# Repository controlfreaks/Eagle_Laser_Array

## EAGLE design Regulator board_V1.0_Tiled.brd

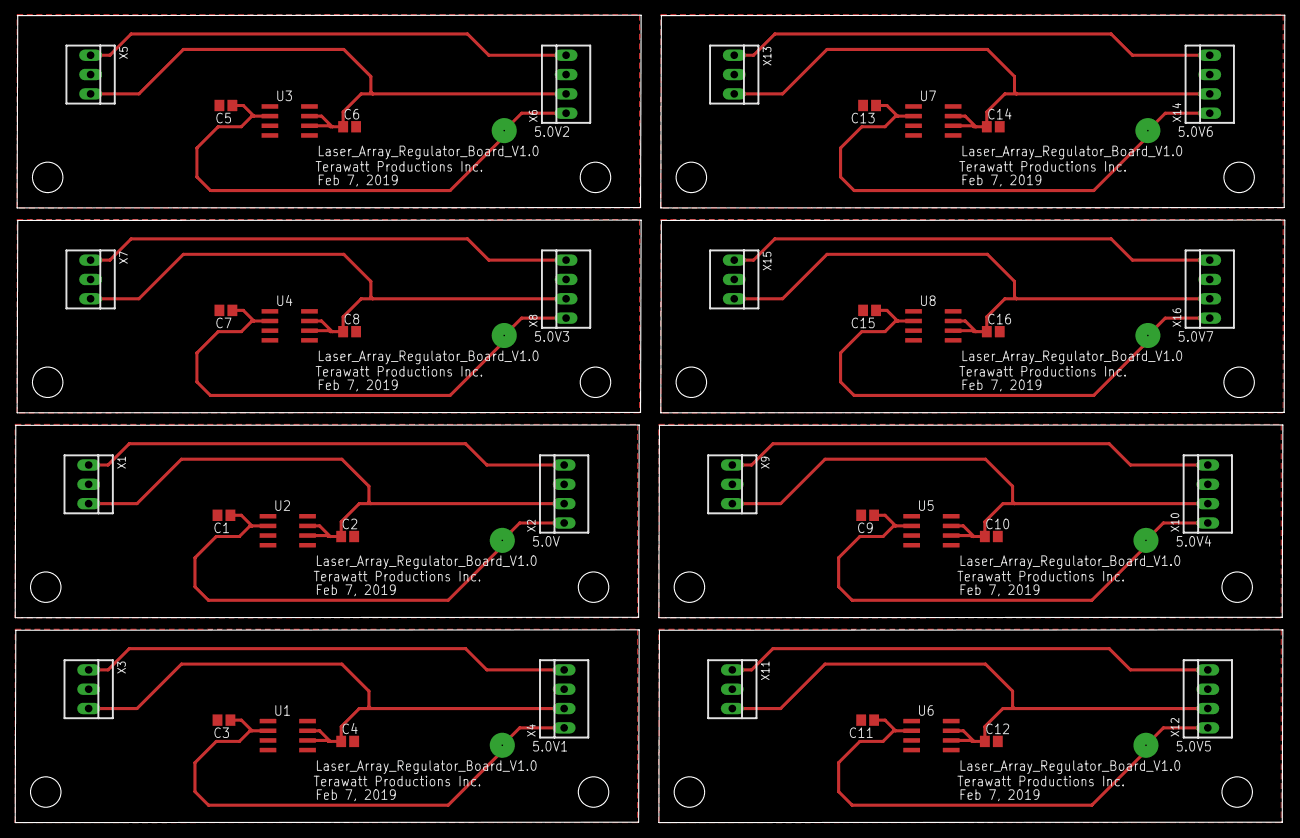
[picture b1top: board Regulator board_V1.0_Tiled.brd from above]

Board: 2 copper layers, 166.8 x 106.1 mm, 48 parts (0 on the bottom side), 32 nets.

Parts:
5.0V, 5.0V1, 5.0V2, 5.0V3, 5.0V4, 5.0V5, 5.0V6, 5.0V7: CONTACT-2MM
C1, C2, C3, C4, C5, C6, C7, C8, C9, C10, C11, C12, C13, C14, C15, C16: 1uF; C0805
U1, U2, U3, U4, U5, U6, U7, U8: VOLTAGE_REG_APD1154ADL; SOIC8
X1, X3, X5, X7, X9, X11, X13, X15: 22-23-2031
X2, X4, X6, X8, X10, X12, X14, X16: 22-23-2041

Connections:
GND: C1.2, C2.2, U2.1, U2.3, U2.4, U2.5, U2.8, X1.2, X2.3
GND1: C3.2, C4.2, U1.1, U1.3, U1.4, U1.5, U1.8, X3.2, X4.3
GND2: C5.2, C6.2, U3.1, U3.3, U3.4, U3.5, U3.8, X5.2, X6.3
GND3: C7.2, C8.2, U4.1, U4.3, U4.4, U4.5, U4.8, X7.2, X8.3
GND4: C9.2, C10.2, U5.1, U5.3, U5.4, U5.5, U5.8, X9.2, X10.3
GND5: C11.2, C12.2, U6.1, U6.3, U6.4, U6.5, U6.8, X11.2, X12.3
GND6: C13.2, C14.2, U7.1, U7.3, U7.4, U7.5, U7.8, X13.2, X14.3
GND7: C15.2, C16.2, U8.1, U8.3, U8.4, U8.5, U8.8, X15.2, X16.3
unnamed: X1.1, X2.4
unnamed: C2.1, U2.6, U2.7, X1.3, X2.2
unnamed: 5.0V.1, C1.1, U2.2, X2.1
unnamed: X3.1, X4.4
unnamed: C4.1, U1.6, U1.7, X3.3, X4.2
unnamed: 5.0V1.1, C3.1, U1.2, X4.1
unnamed: X5.1, X6.4
unnamed: C6.1, U3.6, U3.7, X5.3, X6.2
unnamed: 5.0V2.1, C5.1, U3.2, X6.1
unnamed: X7.1, X8.4
unnamed: C8.1, U4.6, U4.7, X7.3, X8.2
unnamed: 5.0V3.1, C7.1, U4.2, X8.1
unnamed: X9.1, X10.4
unnamed: C10.1, U5.6, U5.7, X9.3, X10.2
unnamed: 5.0V4.1, C9.1, U5.2, X10.1
unnamed: X11.1, X12.4
unnamed: C12.1, U6.6, U6.7, X11.3, X12.2
unnamed: 5.0V5.1, C11.1, U6.2, X12.1
unnamed: X13.1, X14.4
unnamed: C14.1, U7.6, U7.7, X13.3, X14.2
unnamed: 5.0V6.1, C13.1, U7.2, X14.1
unnamed: X15.1, X16.4
unnamed: C16.1, U8.6, U8.7, X15.3, X16.2
unnamed: 5.0V7.1, C15.1, U8.2, X16.1

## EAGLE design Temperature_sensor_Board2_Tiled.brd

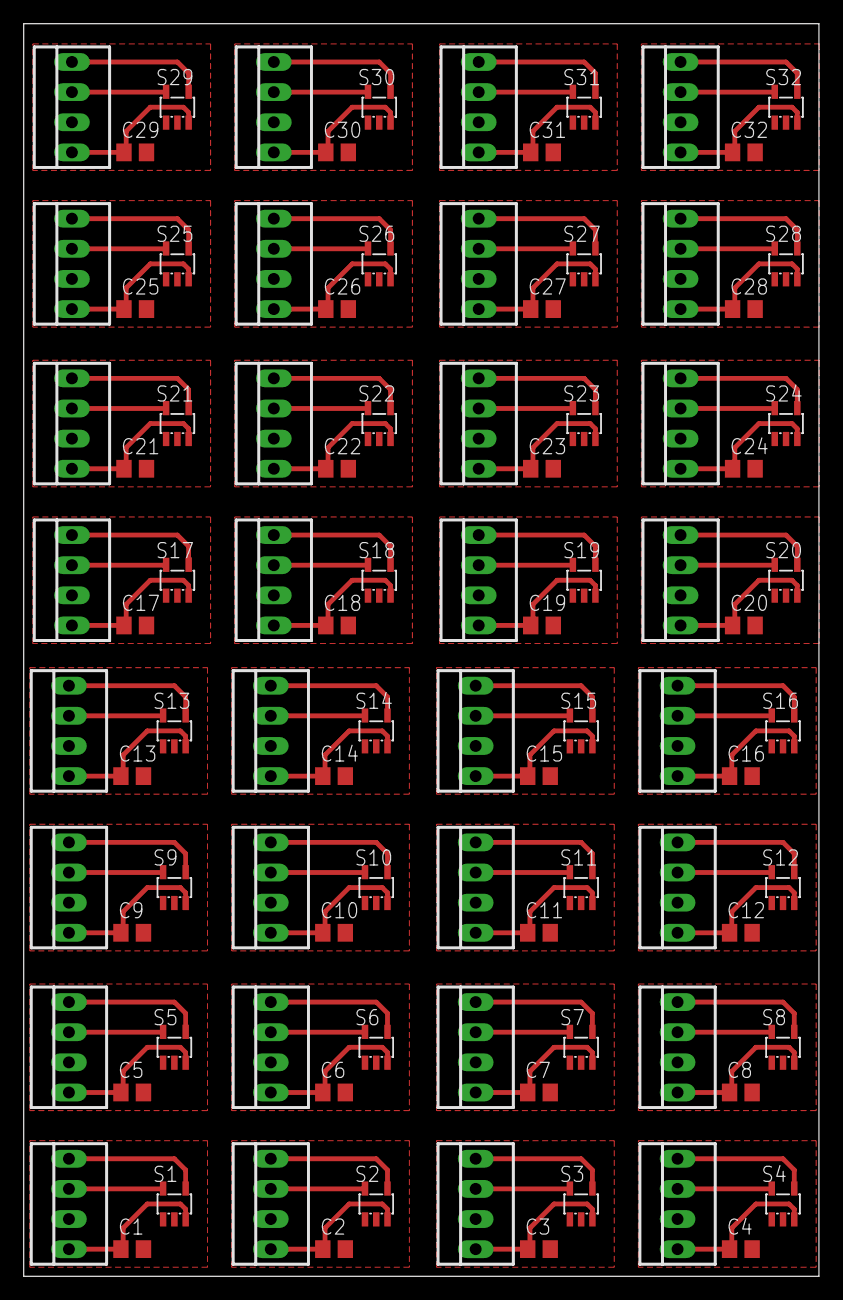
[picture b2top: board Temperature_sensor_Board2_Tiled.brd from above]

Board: 2 copper layers, 67.0 x 105.6 mm, 96 parts (0 on the bottom side), 128 nets.

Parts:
C1, C2, C3, C4, C5, C6, C7, C8, C9, C10, C11, C12, C13, C14, C15, C16, C17, C18, C19, C20, C21, C22, C23, C24, C25, C26, C27, C28, C29, C30, C31, C32: 0.01uF; C0805
S1, S2, S3, S4, S5, S6, S7, S8, S9, S10, S11, S12, S13, S14, S15, S16, S17, S18, S19, S20, S21, S22, S23, S24, S25, S26, S27, S28, S29, S30, S31, S32: TC74; SOT23-5L
X1, X2, X3, X4, X5, X6, X7, X8, X9, X10, X11, X12, X13, X14, X15, X16, X17, X18, X19, X20, X21, X22, X23, X24, X25, X26, X27, X28, X29, X30, X31, X32: 22-23-2041

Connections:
GND: C1.2, S1.2, X1.2
GND1: C2.2, S2.2, X2.2
GND2: C3.2, S3.2, X3.2
GND3: C4.2, S4.2, X4.2
GND4: C5.2, S5.2, X5.2
GND5: C6.2, S6.2, X6.2
GND6: C7.2, S7.2, X7.2
GND7: C8.2, S8.2, X8.2
GND8: C9.2, S9.2, X9.2
GND9: C10.2, S10.2, X10.2
GND10: C11.2, S11.2, X11.2
GND11: C12.2, S12.2, X12.2
GND12: C13.2, S13.2, X13.2
GND13: C14.2, S14.2, X14.2
GND14: C15.2, S15.2, X15.2
GND15: C16.2, S16.2, X16.2
GND16: C17.2, S17.2, X17.2
GND17: C18.2, S18.2, X18.2
GND18: C19.2, S19.2, X19.2
GND19: C20.2, S20.2, X20.2
GND20: C21.2, S21.2, X21.2
GND21: C22.2, S22.2, X22.2
GND22: C23.2, S23.2, X23.2
GND23: C24.2, S24.2, X24.2
GND24: C25.2, S25.2, X25.2
GND25: C26.2, S26.2, X26.2
GND26: C27.2, S27.2, X27.2
GND27: C28.2, S28.2, X28.2
GND28: C29.2, S29.2, X29.2
GND29: C30.2, S30.2, X30.2
GND30: C31.2, S31.2, X31.2
GND31: C32.2, S32.2, X32.2
unnamed: S2.5, X2.3
unnamed: C1.1, S1.3, X1.1
unnamed: S1.5, X1.3
unnamed: S1.4, X1.4
unnamed: S2.4, X2.4
unnamed: C2.1, S2.3, X2.1
unnamed: S3.5, X3.3
unnamed: S3.4, X3.4
unnamed: C3.1, S3.3, X3.1
unnamed: S4.5, X4.3
unnamed: S4.4, X4.4
unnamed: C4.1, S4.3, X4.1
unnamed: S5.5, X5.3
unnamed: S5.4, X5.4
unnamed: C5.1, S5.3, X5.1
unnamed: S6.5, X6.3
unnamed: S6.4, X6.4
unnamed: C6.1, S6.3, X6.1
unnamed: S7.5, X7.3
unnamed: S7.4, X7.4
unnamed: C7.1, S7.3, X7.1
unnamed: S8.5, X8.3
unnamed: S8.4, X8.4
unnamed: C8.1, S8.3, X8.1
unnamed: S9.5, X9.3
unnamed: S9.4, X9.4
unnamed: C9.1, S9.3, X9.1
unnamed: S10.5, X10.3
unnamed: S10.4, X10.4
unnamed: C10.1, S10.3, X10.1
unnamed: S11.5, X11.3
unnamed: S11.4, X11.4
unnamed: C11.1, S11.3, X11.1
unnamed: S12.5, X12.3
unnamed: S12.4, X12.4
unnamed: C12.1, S12.3, X12.1
unnamed: S13.5, X13.3
unnamed: S13.4, X13.4
unnamed: C13.1, S13.3, X13.1
unnamed: S14.5, X14.3
unnamed: S14.4, X14.4
unnamed: C14.1, S14.3, X14.1
unnamed: S15.5, X15.3
unnamed: S15.4, X15.4
unnamed: C15.1, S15.3, X15.1
unnamed: S16.5, X16.3
unnamed: S16.4, X16.4
unnamed: C16.1, S16.3, X16.1
unnamed: S17.5, X17.3
unnamed: S17.4, X17.4
unnamed: C17.1, S17.3, X17.1
unnamed: S18.5, X18.3
unnamed: S18.4, X18.4
unnamed: C18.1, S18.3, X18.1
unnamed: S19.5, X19.3
unnamed: S19.4, X19.4
unnamed: C19.1, S19.3, X19.1
unnamed: S20.5, X20.3
unnamed: S20.4, X20.4
unnamed: C20.1, S20.3, X20.1
unnamed: S21.5, X21.3
unnamed: S21.4, X21.4
unnamed: C21.1, S21.3, X21.1
unnamed: S22.5, X22.3
unnamed: S22.4, X22.4
unnamed: C22.1, S22.3, X22.1
unnamed: S23.5, X23.3
unnamed: S23.4, X23.4
unnamed: C23.1, S23.3, X23.1
unnamed: S24.5, X24.3
unnamed: S24.4, X24.4
unnamed: C24.1, S24.3, X24.1
unnamed: S25.5, X25.3
unnamed: S25.4, X25.4
unnamed: C25.1, S25.3, X25.1
unnamed: S26.5, X26.3
unnamed: S26.4, X26.4
unnamed: C26.1, S26.3, X26.1
unnamed: S27.5, X27.3
unnamed: S27.4, X27.4
unnamed: C27.1, S27.3, X27.1
unnamed: S28.5, X28.3
unnamed: S28.4, X28.4
unnamed: C28.1, S28.3, X28.1
unnamed: S29.5, X29.3
unnamed: S29.4, X29.4
unnamed: C29.1, S29.3, X29.1
unnamed: S30.5, X30.3
unnamed: S30.4, X30.4
unnamed: C30.1, S30.3, X30.1
unnamed: S31.5, X31.3
unnamed: S31.4, X31.4
unnamed: C31.1, S31.3, X31.1
unnamed: S32.5, X32.3
unnamed: S32.4, X32.4
unnamed: C32.1, S32.3, X32.1

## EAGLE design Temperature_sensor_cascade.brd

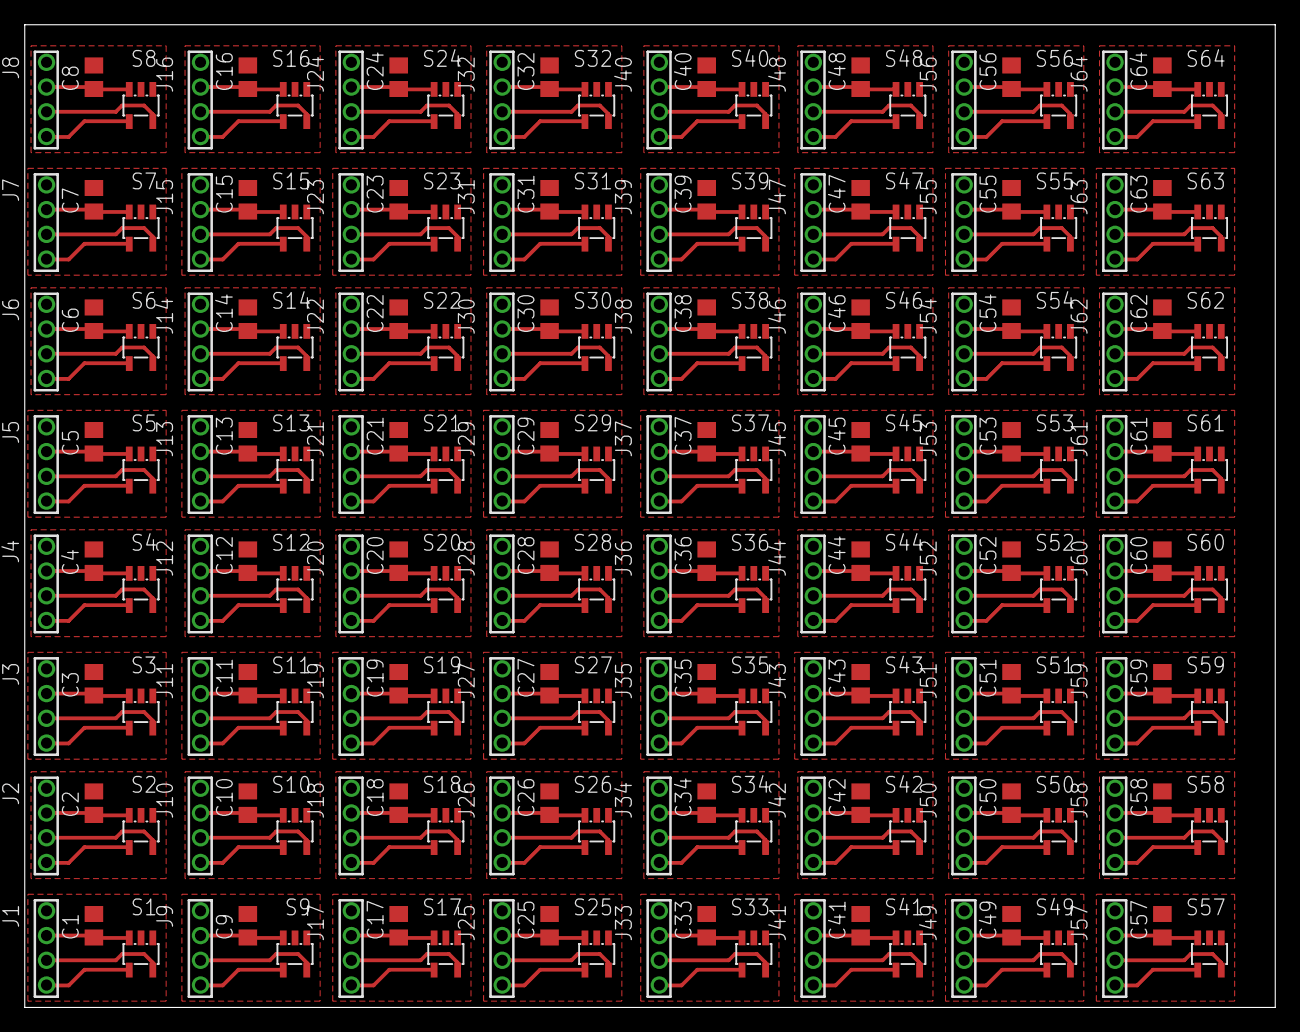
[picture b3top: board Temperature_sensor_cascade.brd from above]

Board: 2 copper layers, 101.1 x 79.4 mm, 192 parts (0 on the bottom side), 256 nets.

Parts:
C1, C2, C3, C4, C5, C6, C7, C8, C9, C10, C11, C12, C13, C14, C15, C16, C17, C18, C19, C20, C21, C22, C23, C24, C25, C26, C27, C28, C29, C30, C31, C32, C33, C34, C35, C36, C37, C38, C39, C40, C41, C42, C43, C44, C45, C46, C47, C48, C49, C50, C51, C52, C53, C54, C55, C56, C57, C58, C59, C60, C61, C62, C63, C64: 0.01uF; C0805
J1, J2, J3, J4, J5, J6, J7, J8, J9, J10, J11, J12, J13, J14, J15, J16, J17, J18, J19, J20, J21, J22, J23, J24, J25, J26, J27, J28, J29, J30, J31, J32, J33, J34, J35, J36, J37, J38, J39, J40, J41, J42, J43, J44, J45, J46, J47, J48, J49, J50, J51, J52, J53, J54, J55, J56, J57, J58, J59, J60, J61, J62, J63, J64: 4_PIN_2MM; 2MM_4PIN
S1, S2, S3, S4, S5, S6, S7, S8, S9, S10, S11, S12, S13, S14, S15, S16, S17, S18, S19, S20, S21, S22, S23, S24, S25, S26, S27, S28, S29, S30, S31, S32, S33, S34, S35, S36, S37, S38, S39, S40, S41, S42, S43, S44, S45, S46, S47, S48, S49, S50, S51, S52, S53, S54, S55, S56, S57, S58, S59, S60, S61, S62, S63, S64: TC74; SOT23-5L

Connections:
GND: C1.2, J1.2, S1.2
GND1: C2.2, J2.2, S2.2
GND2: C3.2, J3.2, S3.2
GND3: C4.2, J4.2, S4.2
GND4: C5.2, J5.2, S5.2
GND5: C6.2, J6.2, S6.2
GND6: C7.2, J7.2, S7.2
GND7: C8.2, J8.2, S8.2
GND8: C9.2, J9.2, S9.2
GND9: C10.2, J10.2, S10.2
GND10: C11.2, J11.2, S11.2
GND11: C12.2, J12.2, S12.2
GND12: C13.2, J13.2, S13.2
GND13: C14.2, J14.2, S14.2
GND14: C15.2, J15.2, S15.2
GND15: C16.2, J16.2, S16.2
GND16: C17.2, J17.2, S17.2
GND17: C18.2, J18.2, S18.2
GND18: C19.2, J19.2, S19.2
GND19: C20.2, J20.2, S20.2
GND20: C21.2, J21.2, S21.2
GND21: C22.2, J22.2, S22.2
GND22: C23.2, J23.2, S23.2
GND23: C24.2, J24.2, S24.2
GND24: C25.2, J25.2, S25.2
GND25: C26.2, J26.2, S26.2
GND26: C27.2, J27.2, S27.2
GND27: C28.2, J28.2, S28.2
GND28: C29.2, J29.2, S29.2
GND29: C30.2, J30.2, S30.2
GND30: C31.2, J31.2, S31.2
GND31: C32.2, J32.2, S32.2
GND32: C33.2, J33.2, S33.2
GND33: C34.2, J34.2, S34.2
GND34: C35.2, J35.2, S35.2
GND35: C36.2, J36.2, S36.2
GND36: C37.2, J37.2, S37.2
GND37: C38.2, J38.2, S38.2
GND38: C39.2, J39.2, S39.2
GND39: C40.2, J40.2, S40.2
GND40: C41.2, J41.2, S41.2
GND41: C42.2, J42.2, S42.2
GND42: C43.2, J43.2, S43.2
GND43: C44.2, J44.2, S44.2
GND44: C45.2, J45.2, S45.2
GND45: C46.2, J46.2, S46.2
GND46: C47.2, J47.2, S47.2
GND47: C48.2, J48.2, S48.2
GND48: C49.2, J49.2, S49.2
GND49: C50.2, J50.2, S50.2
GND50: C51.2, J51.2, S51.2
GND51: C52.2, J52.2, S52.2
GND52: C53.2, J53.2, S53.2
GND53: C54.2, J54.2, S54.2
GND54: C55.2, J55.2, S55.2
GND55: C56.2, J56.2, S56.2
GND56: C57.2, J57.2, S57.2
GND57: C58.2, J58.2, S58.2
GND58: C59.2, J59.2, S59.2
GND59: C60.2, J60.2, S60.2
GND60: C61.2, J61.2, S61.2
GND61: C62.2, J62.2, S62.2
GND62: C63.2, J63.2, S63.2
GND63: C64.2, J64.2, S64.2
unnamed: J2.6, S2.5
unnamed: C1.1, J1.4, S1.3
unnamed: J1.6, S1.5
unnamed: J1.8, S1.4
unnamed: J2.8, S2.4
unnamed: C2.1, J2.4, S2.3
unnamed: J3.6, S3.5
unnamed: J3.8, S3.4
unnamed: C3.1, J3.4, S3.3
unnamed: J4.6, S4.5
unnamed: J4.8, S4.4
unnamed: C4.1, J4.4, S4.3
unnamed: J5.6, S5.5
unnamed: J5.8, S5.4
unnamed: C5.1, J5.4, S5.3
unnamed: J6.6, S6.5
unnamed: J6.8, S6.4
unnamed: C6.1, J6.4, S6.3
unnamed: J7.6, S7.5
unnamed: J7.8, S7.4
unnamed: C7.1, J7.4, S7.3
unnamed: J8.6, S8.5
unnamed: J8.8, S8.4
unnamed: C8.1, J8.4, S8.3
unnamed: J9.6, S9.5
unnamed: J9.8, S9.4
unnamed: C9.1, J9.4, S9.3
unnamed: J10.6, S10.5
unnamed: J10.8, S10.4
unnamed: C10.1, J10.4, S10.3
unnamed: J11.6, S11.5
unnamed: J11.8, S11.4
unnamed: C11.1, J11.4, S11.3
unnamed: J12.6, S12.5
unnamed: J12.8, S12.4
unnamed: C12.1, J12.4, S12.3
unnamed: J13.6, S13.5
unnamed: J13.8, S13.4
unnamed: C13.1, J13.4, S13.3
unnamed: J14.6, S14.5
unnamed: J14.8, S14.4
unnamed: C14.1, J14.4, S14.3
unnamed: J15.6, S15.5
unnamed: J15.8, S15.4
unnamed: C15.1, J15.4, S15.3
unnamed: J16.6, S16.5
unnamed: J16.8, S16.4
unnamed: C16.1, J16.4, S16.3
unnamed: J17.6, S17.5
unnamed: J17.8, S17.4
unnamed: C17.1, J17.4, S17.3
unnamed: J18.6, S18.5
unnamed: J18.8, S18.4
unnamed: C18.1, J18.4, S18.3
unnamed: J19.6, S19.5
unnamed: J19.8, S19.4
unnamed: C19.1, J19.4, S19.3
unnamed: J20.6, S20.5
unnamed: J20.8, S20.4
unnamed: C20.1, J20.4, S20.3
unnamed: J21.6, S21.5
unnamed: J21.8, S21.4
unnamed: C21.1, J21.4, S21.3
unnamed: J22.6, S22.5
unnamed: J22.8, S22.4
unnamed: C22.1, J22.4, S22.3
unnamed: J23.6, S23.5
unnamed: J23.8, S23.4
unnamed: C23.1, J23.4, S23.3
unnamed: J24.6, S24.5
unnamed: J24.8, S24.4
unnamed: C24.1, J24.4, S24.3
unnamed: J25.6, S25.5
unnamed: J25.8, S25.4
unnamed: C25.1, J25.4, S25.3
unnamed: J26.6, S26.5
unnamed: J26.8, S26.4
unnamed: C26.1, J26.4, S26.3
unnamed: J27.6, S27.5
unnamed: J27.8, S27.4
unnamed: C27.1, J27.4, S27.3
unnamed: J28.6, S28.5
unnamed: J28.8, S28.4
unnamed: C28.1, J28.4, S28.3
unnamed: J29.6, S29.5
unnamed: J29.8, S29.4
unnamed: C29.1, J29.4, S29.3
unnamed: J30.6, S30.5
unnamed: J30.8, S30.4
unnamed: C30.1, J30.4, S30.3
unnamed: J31.6, S31.5
unnamed: J31.8, S31.4
unnamed: C31.1, J31.4, S31.3
unnamed: J32.6, S32.5
unnamed: J32.8, S32.4
unnamed: C32.1, J32.4, S32.3
unnamed: J33.6, S33.5
unnamed: J33.8, S33.4
unnamed: C33.1, J33.4, S33.3
unnamed: J34.6, S34.5
unnamed: J34.8, S34.4
unnamed: C34.1, J34.4, S34.3
unnamed: J35.6, S35.5
unnamed: J35.8, S35.4
unnamed: C35.1, J35.4, S35.3
unnamed: J36.6, S36.5
unnamed: J36.8, S36.4
unnamed: C36.1, J36.4, S36.3
unnamed: J37.6, S37.5
unnamed: J37.8, S37.4
unnamed: C37.1, J37.4, S37.3
unnamed: J38.6, S38.5
unnamed: J38.8, S38.4
unnamed: C38.1, J38.4, S38.3
unnamed: J39.6, S39.5
unnamed: J39.8, S39.4
unnamed: C39.1, J39.4, S39.3
unnamed: J40.6, S40.5
unnamed: J40.8, S40.4
unnamed: C40.1, J40.4, S40.3
unnamed: J41.6, S41.5
unnamed: J41.8, S41.4
unnamed: C41.1, J41.4, S41.3
unnamed: J42.6, S42.5
unnamed: J42.8, S42.4
unnamed: C42.1, J42.4, S42.3
unnamed: J43.6, S43.5
unnamed: J43.8, S43.4
unnamed: C43.1, J43.4, S43.3
unnamed: J44.6, S44.5
unnamed: J44.8, S44.4
unnamed: C44.1, J44.4, S44.3
unnamed: J45.6, S45.5
unnamed: J45.8, S45.4
unnamed: C45.1, J45.4, S45.3
unnamed: J46.6, S46.5
unnamed: J46.8, S46.4
unnamed: C46.1, J46.4, S46.3
unnamed: J47.6, S47.5
unnamed: J47.8, S47.4
unnamed: C47.1, J47.4, S47.3
unnamed: J48.6, S48.5
unnamed: J48.8, S48.4
unnamed: C48.1, J48.4, S48.3
unnamed: J49.6, S49.5
unnamed: J49.8, S49.4
unnamed: C49.1, J49.4, S49.3
unnamed: J50.6, S50.5
unnamed: J50.8, S50.4
unnamed: C50.1, J50.4, S50.3
unnamed: J51.6, S51.5
unnamed: J51.8, S51.4
unnamed: C51.1, J51.4, S51.3
unnamed: J52.6, S52.5
unnamed: J52.8, S52.4
unnamed: C52.1, J52.4, S52.3
unnamed: J53.6, S53.5
unnamed: J53.8, S53.4
unnamed: C53.1, J53.4, S53.3
unnamed: J54.6, S54.5
unnamed: J54.8, S54.4
unnamed: C54.1, J54.4, S54.3
unnamed: J55.6, S55.5
unnamed: J55.8, S55.4
unnamed: C55.1, J55.4, S55.3
unnamed: J56.6, S56.5
unnamed: J56.8, S56.4
unnamed: C56.1, J56.4, S56.3
unnamed: J57.6, S57.5
unnamed: J57.8, S57.4
unnamed: C57.1, J57.4, S57.3
unnamed: J58.6, S58.5
unnamed: J58.8, S58.4
unnamed: C58.1, J58.4, S58.3
unnamed: J59.6, S59.5
unnamed: J59.8, S59.4
unnamed: C59.1, J59.4, S59.3
unnamed: J60.6, S60.5
unnamed: J60.8, S60.4
unnamed: C60.1, J60.4, S60.3
unnamed: J61.6, S61.5
unnamed: J61.8, S61.4
unnamed: C61.1, J61.4, S61.3
unnamed: J62.6, S62.5
unnamed: J62.8, S62.4
unnamed: C62.1, J62.4, S62.3
unnamed: J63.6, S63.5
unnamed: J63.8, S63.4
unnamed: C63.1, J63.4, S63.3
unnamed: J64.6, S64.5
unnamed: J64.8, S64.4
unnamed: C64.1, J64.4, S64.3
